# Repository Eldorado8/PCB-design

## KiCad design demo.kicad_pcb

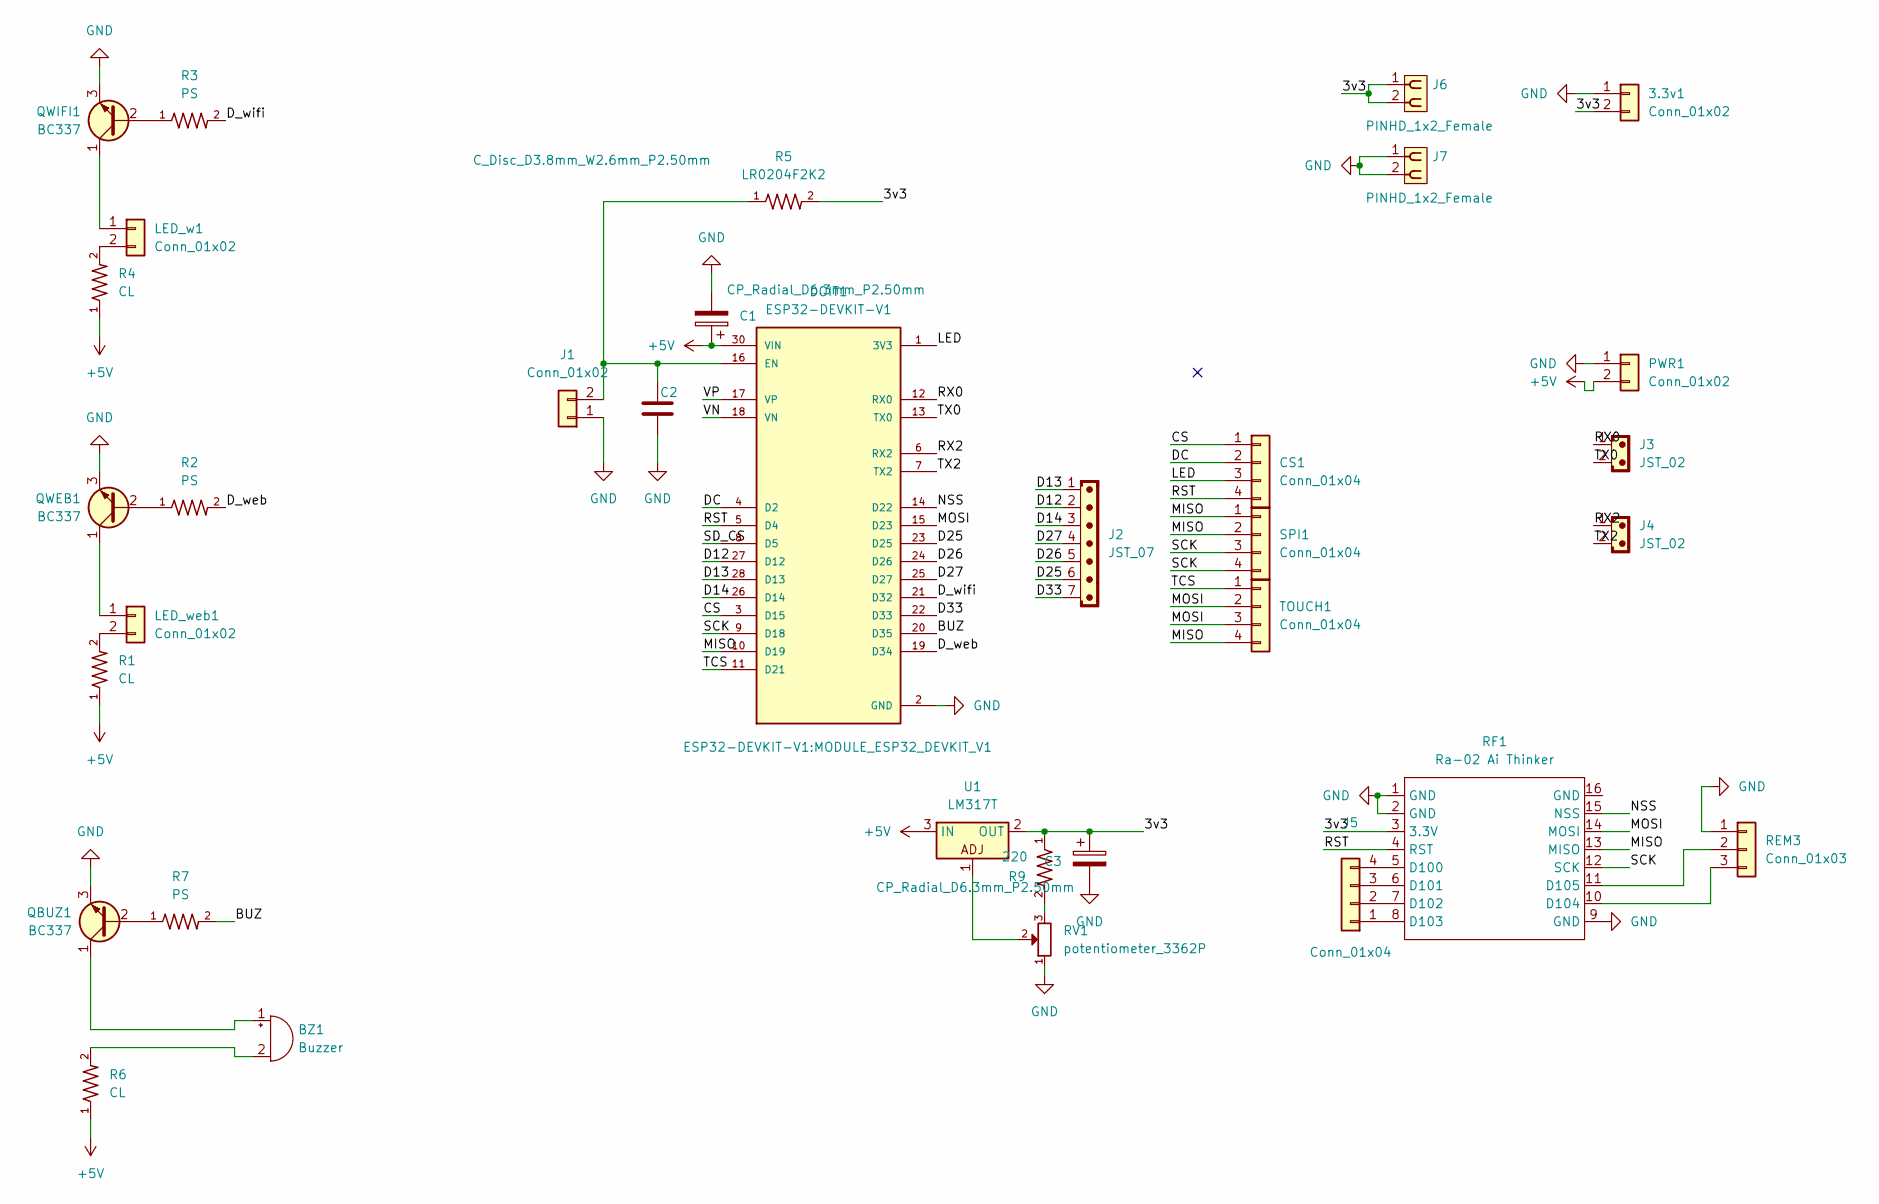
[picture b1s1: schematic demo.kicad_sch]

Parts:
3.3v1: Conn_01x02; TerminalBlock_Phoenix_MKDS-1,5-2_1x02_P5.00mm_Horizontal
BZ1: Buzzer; Buzzer_12x9.5RM7.6
C1, C3: CP_Radial_D6.3mm_P2.50mm
C2: C_Disc_D3.8mm_W2.6mm_P2.50mm
CS1: Conn_01x04; JST_XH_B4B-XH-A_1x04_P2.50mm_Vertical
DOIT1: ESP32-DEVKIT-V1; MODULE_ESP32_DEVKIT_V1; PARTREV N/A
J1: Conn_01x02; JST_XH_B2B-XH-A_1x02_P2.50mm_Vertical
J2: JST_07; PinHeader_1x07_P2.54mm_Vertical
J3, J4: JST_02; JST_EH_B2B-EH-A_1x02_P2.50mm_Vertical
J5: Conn_01x04; PinHeader_1x04_P2.54mm_Vertical
J6, J7: PINHD_1x2_Female; PinSocket_1x02_P2.54mm_Vertical
LED_w1: Conn_01x02; JST_XH_B2B-XH-A_1x02_P2.50mm_Vertical
LED_web1: Conn_01x02; JST_XH_B2B-XH-A_1x02_P2.50mm_Vertical
PWR1: Conn_01x02; TerminalBlock_Phoenix_MKDS-1,5-2_1x02_P5.00mm_Horizontal
QBUZ1: BC337; TO-92_Inline_Wide_CBE
QWEB1: BC337; TO-92_Inline_Wide_CBE
QWIFI1: BC337; TO-92_Inline_Wide_CBE
R1, R4, R6: CL; RESAD640W45L370D200
R2, R3, R7: PS; RESAD640W45L370D200
R5: LR0204F2K2; RESAD640W45L370D200
R9: 220; RESAD640W45L370D200
REM3: Conn_01x03; PinHeader_1x03_P2.54mm_Vertical
RF1: Ra-02 Ai Thinker
RV1: potentiometer_3362P
SPI1: Conn_01x04; JST_XH_B4B-XH-A_1x04_P2.50mm_Vertical
TOUCH1: Conn_01x04; JST_XH_B4B-XH-A_1x04_P2.50mm_Vertical
U1: LM317T; TO-220-3_Vertical

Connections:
+5V: C1.1, DOIT1.30 (VIN), PWR1.2, R1.1, R4.1, R6.1, U1.3 (IN)
/3v3: 3.3v1.2, C3.1, J6.1, J6.2, R5.2, R9.1, RF1.3 (3.3V), U1.2 (OUT)
/<NO NET>: DOIT1.14 (D22), RF1.15 (NSS)
/BUZ: DOIT1.20 (D35), R7.2
/CS: CS1.1, DOIT1.3 (D15)
/D12: DOIT1.27 (D12), J2.2
/D13: DOIT1.28 (D13), J2.1
/D14: DOIT1.26 (D14), J2.3
/D25: DOIT1.23 (D25), J2.6
/D26: DOIT1.24 (D26), J2.5
/D27: DOIT1.25 (D27), J2.4
/D33: DOIT1.22 (D33), J2.7
/DC: CS1.2, DOIT1.4 (D2)
/D_web: DOIT1.19 (D34), R2.2
/D_wifi: DOIT1.21 (D32), R3.2
/LED: CS1.3, DOIT1.1 (3V3)
/MISO: DOIT1.10 (D19), RF1.13 (MISO), SPI1.1, SPI1.2, TOUCH1.4
/MOSI: DOIT1.15 (D23), RF1.14 (MOSI), TOUCH1.2, TOUCH1.3
/RST: CS1.4, DOIT1.5 (D4), RF1.4 (RST)
/RX0: DOIT1.12 (RX0), J3.1
/RX2: DOIT1.6 (RX2), J4.1
/SCK: DOIT1.9 (D18), RF1.12 (SCK), SPI1.3, SPI1.4
/SD_CS: DOIT1.8 (D5)
/TCS: DOIT1.11 (D21), TOUCH1.1
/TX0: DOIT1.13 (TX0), J3.2
/TX2: DOIT1.7 (TX2), J4.2
/VN: DOIT1.18 (VN)
/VP: DOIT1.17 (VP)
GND: 3.3v1.1, C1.2, C2.2, C3.2, DOIT1.2 (GND), DOIT1.29 (GND), J1.1, J7.1, J7.2, PWR1.1, QBUZ1.3 (E), QWEB1.3 (E), QWIFI1.3 (E), REM3.1, RF1.1 (GND), RF1.2 (GND), RF1.9 (GND), RV1.1
unnamed: BZ1.1 (+), QBUZ1.1 (C)
unnamed: BZ1.2 (-), R6.2
unnamed: C2.1, DOIT1.16 (EN), J1.2, R5.1
unnamed: J5.1, RF1.8 (D103)
unnamed: J5.2, RF1.7 (D102)
unnamed: J5.3, RF1.6 (D101)
unnamed: J5.4, RF1.5 (D100)
unnamed: LED_w1.1, QWIFI1.1 (C)
unnamed: LED_w1.2, R4.2
unnamed: LED_web1.1, QWEB1.1 (C)
unnamed: LED_web1.2, R1.2
unnamed: QBUZ1.2 (B), R7.1
unnamed: QWEB1.2 (B), R2.1
unnamed: QWIFI1.2 (B), R3.1
unnamed: R9.2, RV1.3
unnamed: REM3.2, RF1.11 (D105)
unnamed: REM3.3, RF1.10 (D104)
unnamed: RV1.2, U1.1

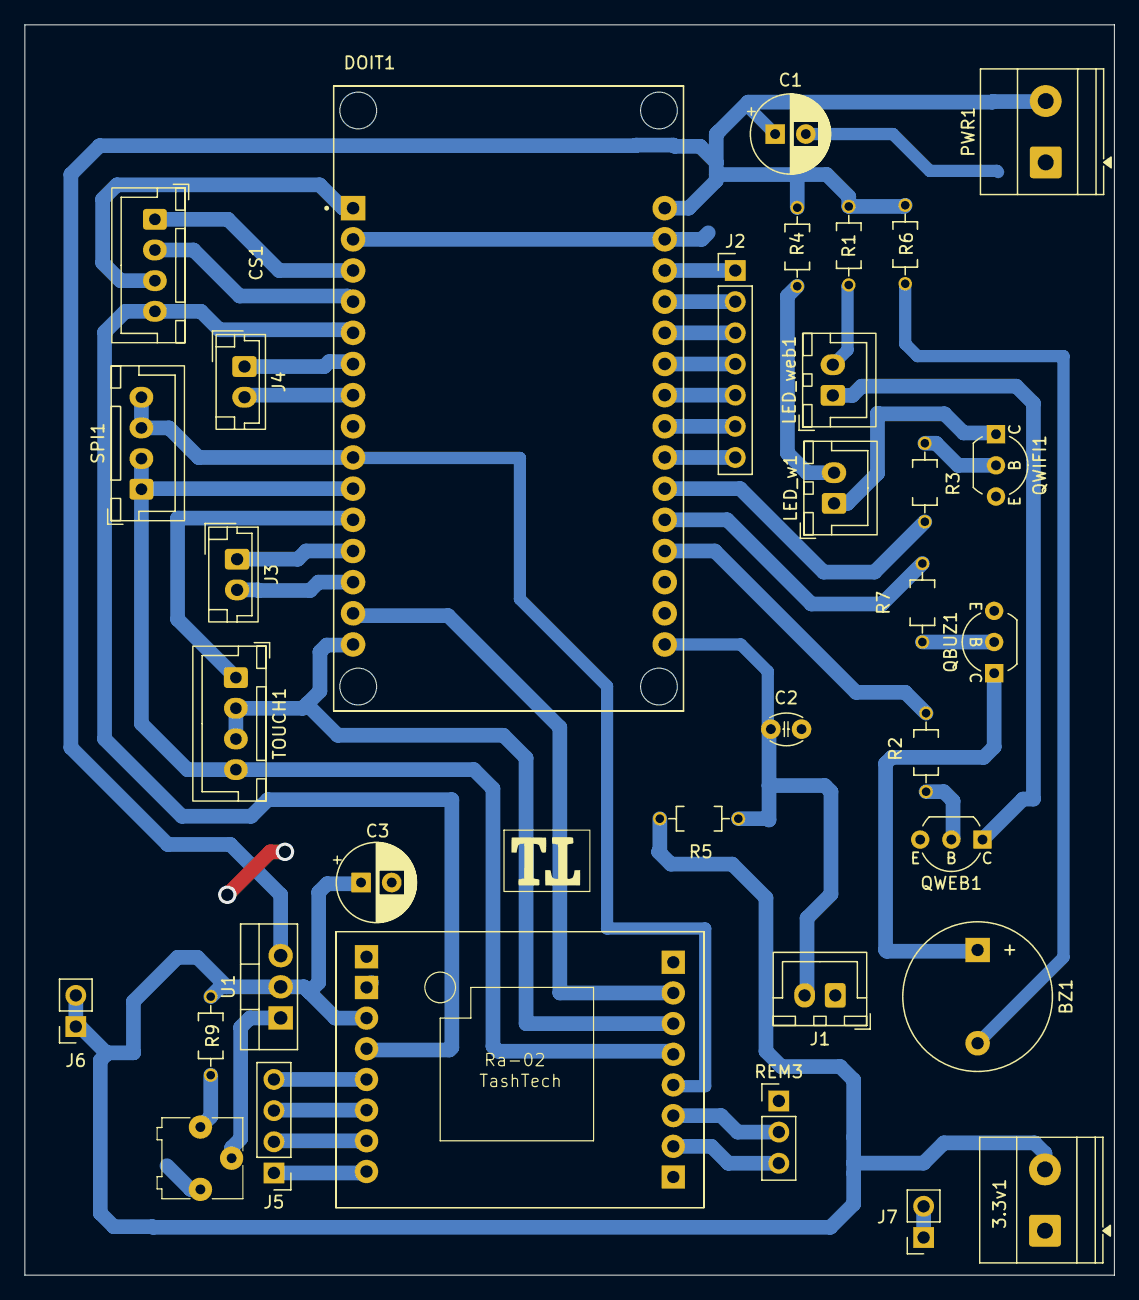
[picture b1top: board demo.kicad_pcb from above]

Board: 2 copper layers, 88.8 x 101.9 mm, 34 parts (0 on the bottom side), 44 nets.

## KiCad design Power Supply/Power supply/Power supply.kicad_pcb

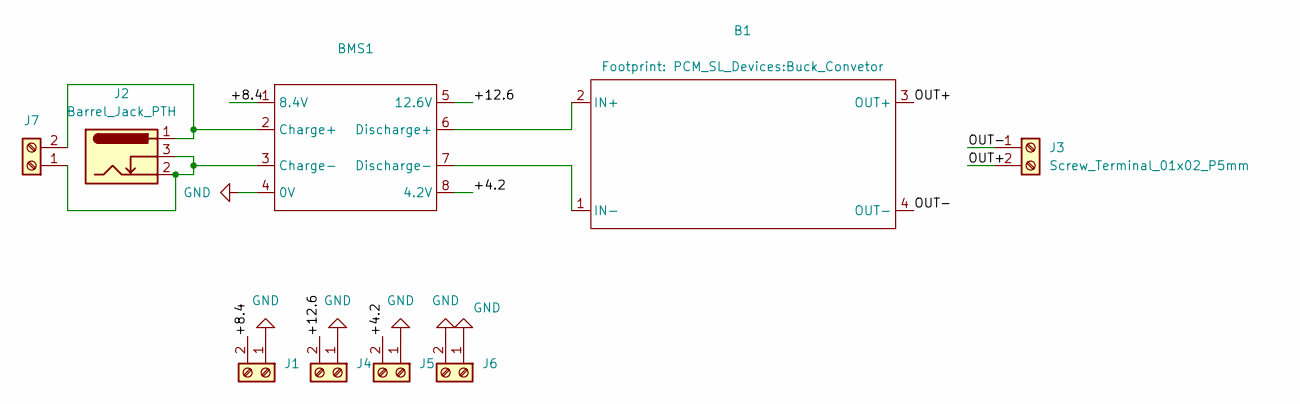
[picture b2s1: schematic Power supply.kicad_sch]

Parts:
B1: Buck_Convetor
BMS1: 3S-BMS
J1, J3, J4, J5, J6, J7: Screw_Terminal_01x02_P5mm; TerminalBlock_Phoenix_MKDS-3-2-5.08_1x02_P5.08mm_Horizontal
J2: Barrel_Jack_PTH

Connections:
/+4.2: BMS1.8 (4.2V), J5.2
/+8.4: BMS1.1 (8.4V), J1.2
/+12.6: BMS1.5 (12.6V), J4.2
/OUT+: B1.3 (OUT+), J3.2
/OUT-: B1.4 (OUT-), J3.1
GND: BMS1.4 (0V), J1.1, J4.1, J5.1, J6.1, J6.2
unnamed: B1.2 (IN+), BMS1.6 (Discharge+)
unnamed: B1.1 (IN-), BMS1.7 (Discharge-)
unnamed: BMS1.2 (Charge+), J2.1 (PWR), J7.2
unnamed: BMS1.3 (Charge-), J2.2 (GND), J2.3 (GNDBREAK), J7.1

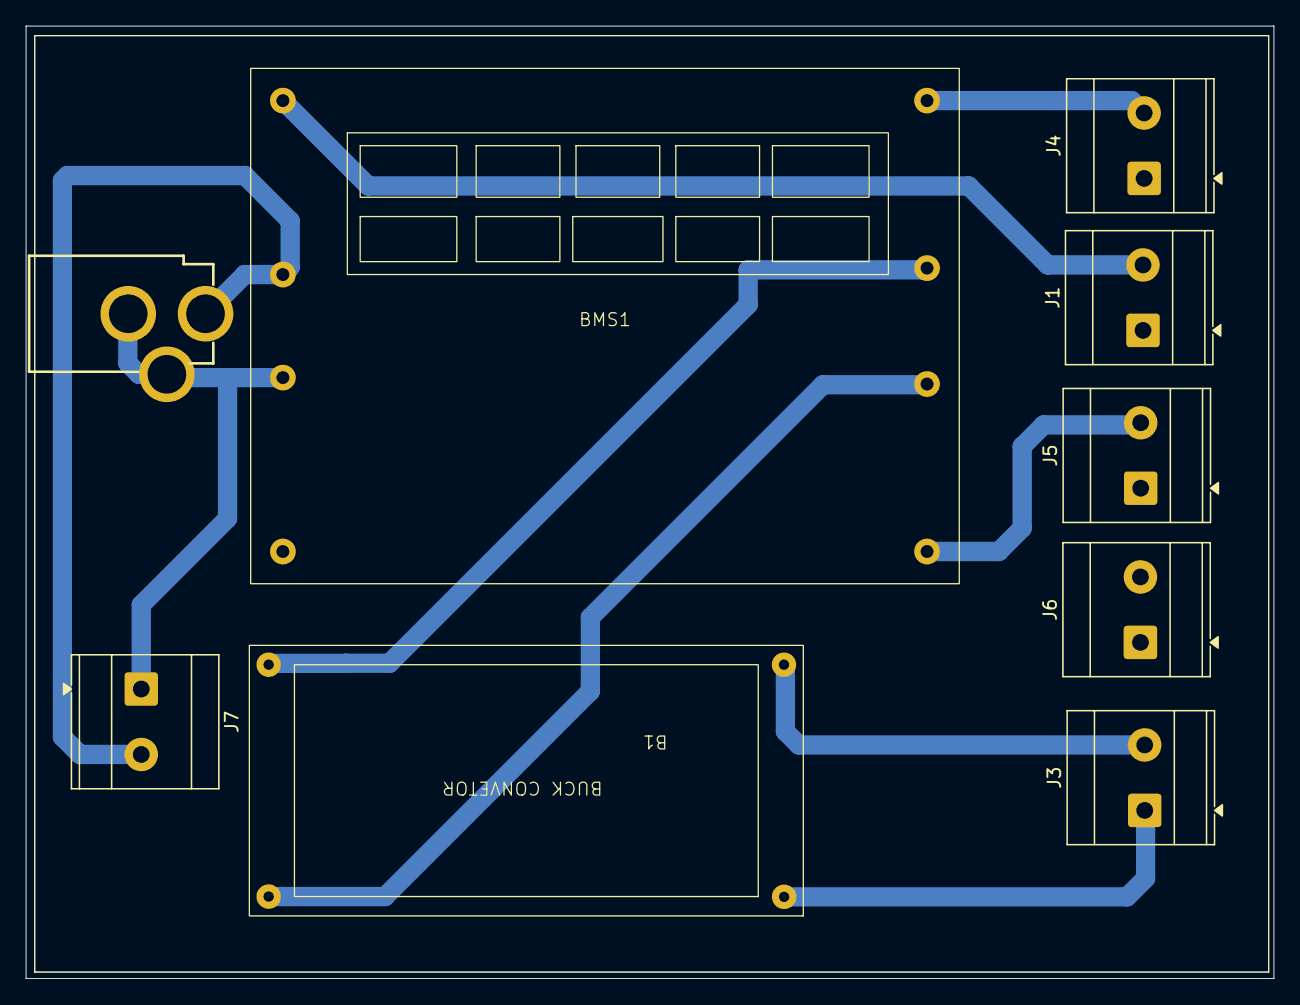
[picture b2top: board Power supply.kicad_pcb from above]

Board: 2 copper layers, 96.9 x 73.9 mm, 9 parts (0 on the bottom side), 10 nets.

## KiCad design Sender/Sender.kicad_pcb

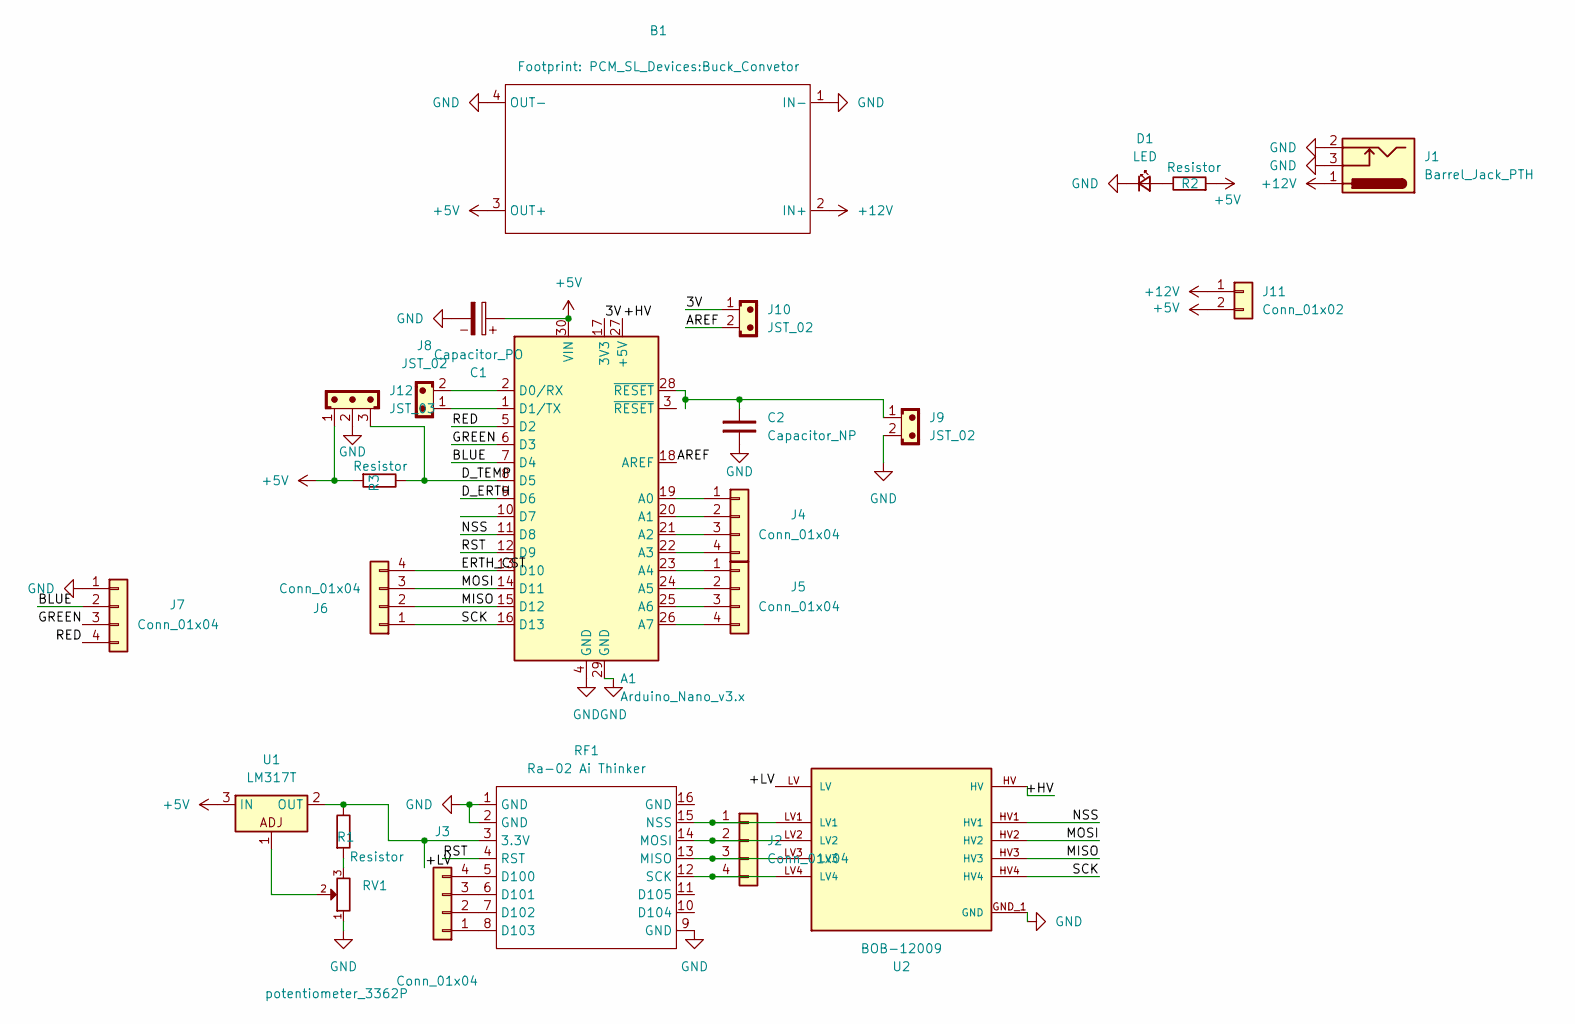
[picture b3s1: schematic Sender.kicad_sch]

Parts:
A1: Arduino_Nano_v3.x; Arduino_Nano
B1: Buck_Convetor
C1: Capacitor_PO; CP_Radial_D5.0mm_P2.50mm
C2: Capacitor_NP; C_Disc_D3.0mm_W2.0mm_P2.50mm
D1: LED; LED_D3.0mm
J1: Barrel_Jack_PTH
J2, J3, J4, J5, J6, J7: Conn_01x04; JST_XH_B4B-XH-A_1x04_P2.50mm_Vertical
J8, J9, J10: JST_02; JST_EH_B2B-EH-A_1x02_P2.50mm_Vertical
J11: Conn_01x02; PinHeader_1x02_P2.54mm_Horizontal
J12: JST_03; JST_EH_B3B-EH-A_1x03_P2.50mm_Vertical
R1, R2, R3: Resistor; R_Axial_DIN0207_L6.3mm_D2.5mm_P10.16mm_Horizontal
RF1: Ra-02 Ai Thinker
RV1: potentiometer_3362P
U1: LM317T; TO-220-3_Vertical
U2: BOB-12009; CONV_BOB-12009; PARTREV 01

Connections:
+5V: A1.30 (VIN), B1.3 (OUT+), C1.1, J11.2, J12.1, R2.1, R3.1, U1.3 (IN)
+12V: B1.2 (IN+), J1.1 (PWR), J11.1
/3V: A1.17 (3V3), J10.1
/+HV: A1.27 (+5V), U2.HV
/+LV: R1.2, RF1.3 (3.3V), U1.2 (OUT), U2.LV
/<NO NET>: A1.7 (D4), J7.2
/AREF: A1.18 (AREF), J10.2
/D_ERTH: A1.9 (D6)
/D_TEMP: A1.8 (D5), J12.3, R3.2
/ERTH_CST: A1.13 (D10), J6.4
/GREEN: A1.6 (D3), J7.3
/MISO: A1.15 (D12), J6.2, U2.HV3
/MOSI: A1.14 (D11), J6.3, U2.HV2
/NSS: A1.11 (D8), U2.HV1
/RED: A1.5 (D2), J7.4
/RST: A1.12 (D9), RF1.4 (RST)
/SCK: A1.16 (D13), J6.1, U2.HV4
GND: A1.4 (GND), A1.29 (GND), B1.1 (IN-), B1.4 (OUT-), C1.2, C2.1, D1.1 (K), J1.2 (GND), J1.3 (GNDBREAK), J7.1, J9.2, J12.2, RF1.1 (GND), RF1.2 (GND), RF1.9 (GND), RV1.1, U2.GND_1 (GND), U2.GND_2 (GND)
unnamed: A1.19 (A0), J4.1
unnamed: A1.20 (A1), J4.2
unnamed: A1.21 (A2), J4.3
unnamed: A1.22 (A3), J4.4
unnamed: A1.23 (A4), J5.1
unnamed: A1.24 (A5), J5.2
unnamed: A1.25 (A6), J5.3
unnamed: A1.26 (A7), J5.4
unnamed: A1.2 (D0/RX), J8.2
unnamed: A1.1 (D1/TX), J8.1
unnamed: A1.28 (~RESET), C2.2, J9.1
unnamed: D1.2 (A), R2.2
unnamed: J2.1, RF1.15 (NSS), U2.LV1
unnamed: J2.2, RF1.14 (MOSI), U2.LV2
unnamed: J2.3, RF1.13 (MISO), U2.LV3
unnamed: J2.4, RF1.12 (SCK), U2.LV4
unnamed: J3.1, RF1.8 (D103)
unnamed: J3.2, RF1.7 (D102)
unnamed: J3.3, RF1.6 (D101)
unnamed: J3.4, RF1.5 (D100)
unnamed: R1.1, RV1.3
unnamed: RV1.2, U1.1

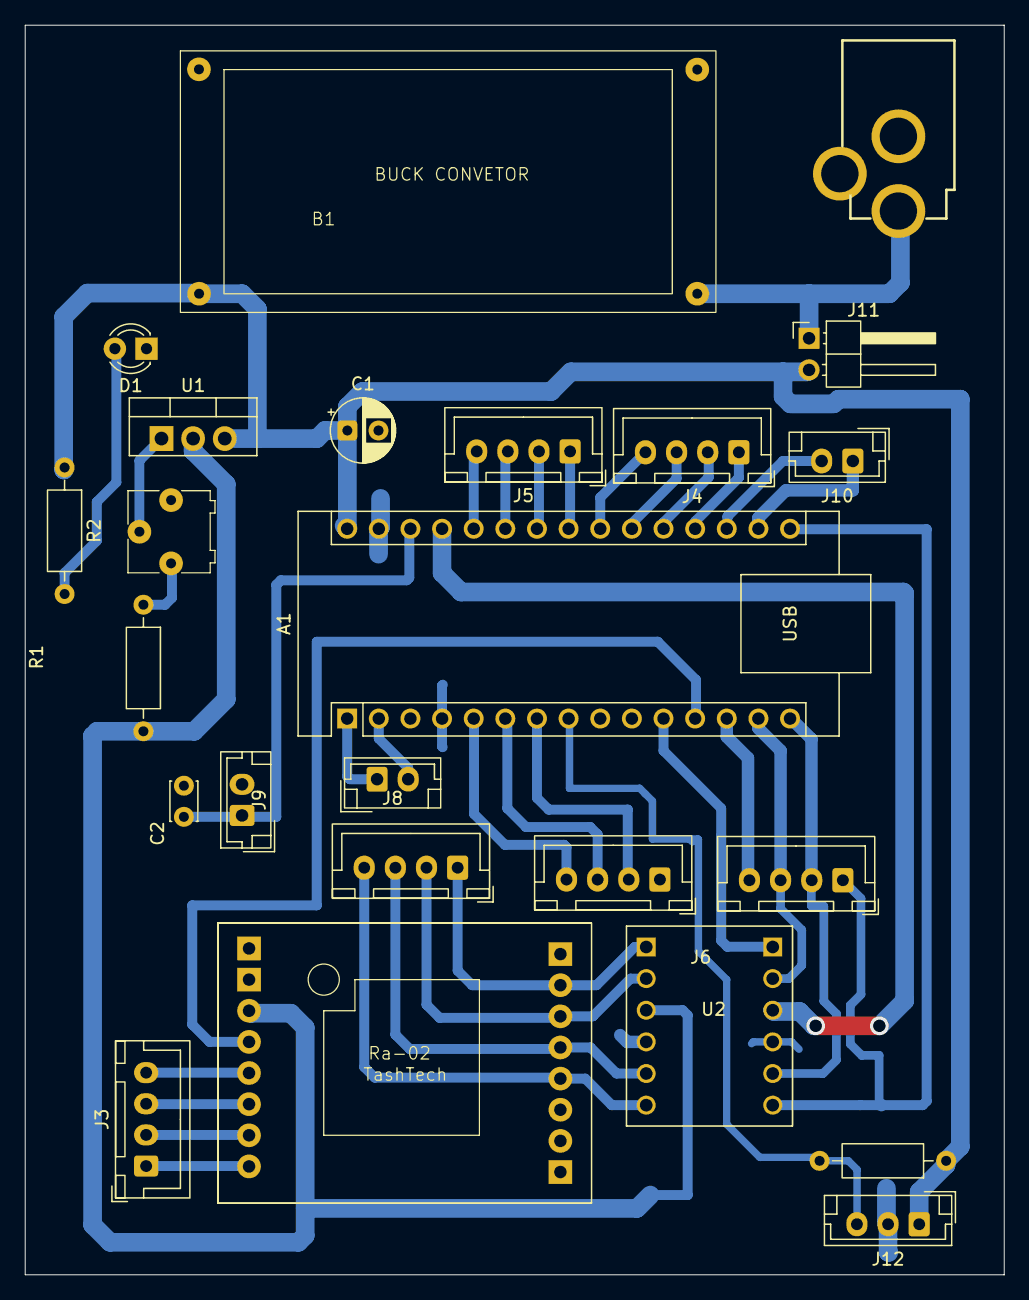
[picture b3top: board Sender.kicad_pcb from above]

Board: 2 copper layers, 78.6 x 100.3 mm, 24 parts (0 on the bottom side), 39 nets.

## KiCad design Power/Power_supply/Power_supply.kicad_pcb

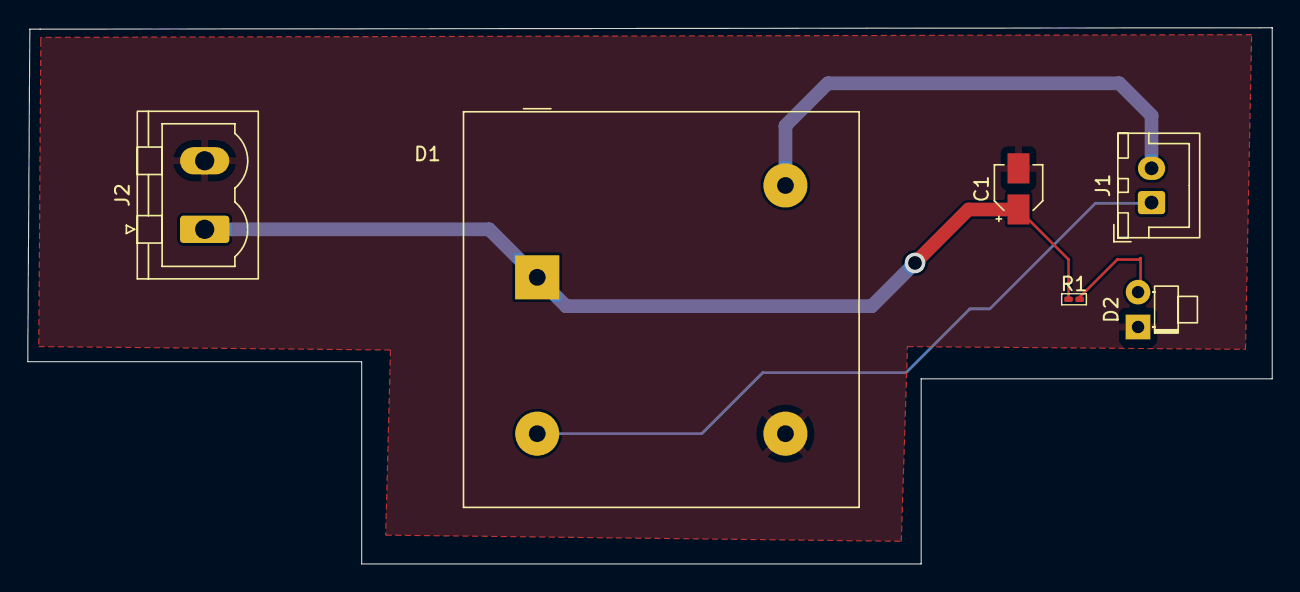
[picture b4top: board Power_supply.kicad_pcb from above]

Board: 2 copper layers, 90.8 x 39.1 mm, 6 parts (0 on the bottom side), 5 nets.

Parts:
C1: C_Polarized; CP_Elec_3x5.3
D1: KBPC1501W; Diode_Bridge_GeneSiC_KBPC_W
D2: LED; LED_D1.8mm_W1.8mm_H2.4mm_Horizontal_O1.27mm_Z1.6mm
J1: Conn_01x02; JST_XH_B2B-XH-A_1x02_P2.50mm_Vertical
J2: Conn_01x02; PhoenixContact_MSTBVA_2,5_2-G_1x02_P5.00mm_Vertical
R1: R; R_0201_0603Metric_Pad0.64x0.40mm

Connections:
/DC+: C1.1, D1.1 (+), J2.1, R1.1
/L: D1.4, J1.1
/N: D1.2, J1.2
GND: C1.2, D1.3 (-), D2.1 (K), J2.2
unnamed: D2.2 (A), R1.2

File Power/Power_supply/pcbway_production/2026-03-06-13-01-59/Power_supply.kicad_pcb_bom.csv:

Designator,Quantity,Value,Footprint,Package,MPN,DNP,Mount_Type,Description,Sim.Pins
C1,1,C_Polarized,CP_Elec_3x5.3,,,,smt,Polarized capacitor,
D1,1,KBPC1501W,Diode_Bridge_GeneSiC_KBPC_W,,,,tht,"Single-Phase Bridge Rectifier, 70V Vrms, 15A If, KBPC-W(WS)",
D2,1,LED,LED_D1.8mm_W1.8mm_H2.4mm_Horizontal_O1.27mm_Z1.6mm,,,,tht,Light emitting diode,1=K 2=A
J1,1,Conn_01x02,JST_XH_B2B-XH-A_1x02_P2.50mm_Vertical,,,,tht,"Generic connector, single row, 01x02, script generated (kicad-library-utils/schlib/autogen/connector/)",
J2,1,Conn_01x02,"PhoenixContact_MSTBVA_2,5_2-G_1x02_P5.00mm_Vertical",,,,tht,"Generic connector, single row, 01x02, script generated (kicad-library-utils/schlib/autogen/connector/)",
R1,1,R,R_0201_0603Metric_Pad0.64x0.40mm,,,,smt,Resistor,

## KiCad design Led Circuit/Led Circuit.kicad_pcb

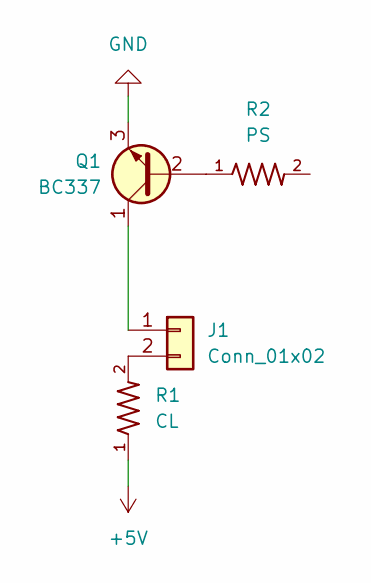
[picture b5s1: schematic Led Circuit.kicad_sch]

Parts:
J1: Conn_01x02; JST_XH_B2B-XH-A_1x02_P2.50mm_Vertical
Q1: BC337; TO-92_Inline_Wide_CBE
R1: CL; RESAD640W45L370D200
R2: PS; RESAD640W45L370D200

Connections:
+5V: R1.1
GND: Q1.3 (E)
unnamed: J1.1, Q1.1 (C)
unnamed: J1.2, R1.2
unnamed: Q1.2 (B), R2.1

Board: 2 copper layers, 4 parts (0 on the bottom side), 3 nets, no tracks yet.

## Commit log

2026-03-01 updated PCB
2026-03-21 uodated pcb with sender
2026-03-23 latest update
2026-03-29 final Update
